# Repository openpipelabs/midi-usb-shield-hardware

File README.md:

OpenPipe MIDI-USB Shield
========================

This is the PCB for the OpenPipe MIDI-USB Shield  
Format is EagleCAD schematic and board layout  

For more details, check out the product page at  
http://openpipe.cc/products/midi-usb-shield/

OpenPipe invests time and resources providing this open source design, 
please support OpenPipe and open-source hardware by purchasing 
products from OpenPipe!

License & Attribution
---------------------
Designed by OpenPipe (www.openpipe.cc).

Creative Commons Attribution-NonCommercial-ShareAlike license (CC BY-NC-SA)

http://creativecommons.org/licenses/by-nc-sa/3.0/  
http://creativecommons.org/licenses/by-nc-sa/3.0/legalcode

All text above must be included in any redistribution

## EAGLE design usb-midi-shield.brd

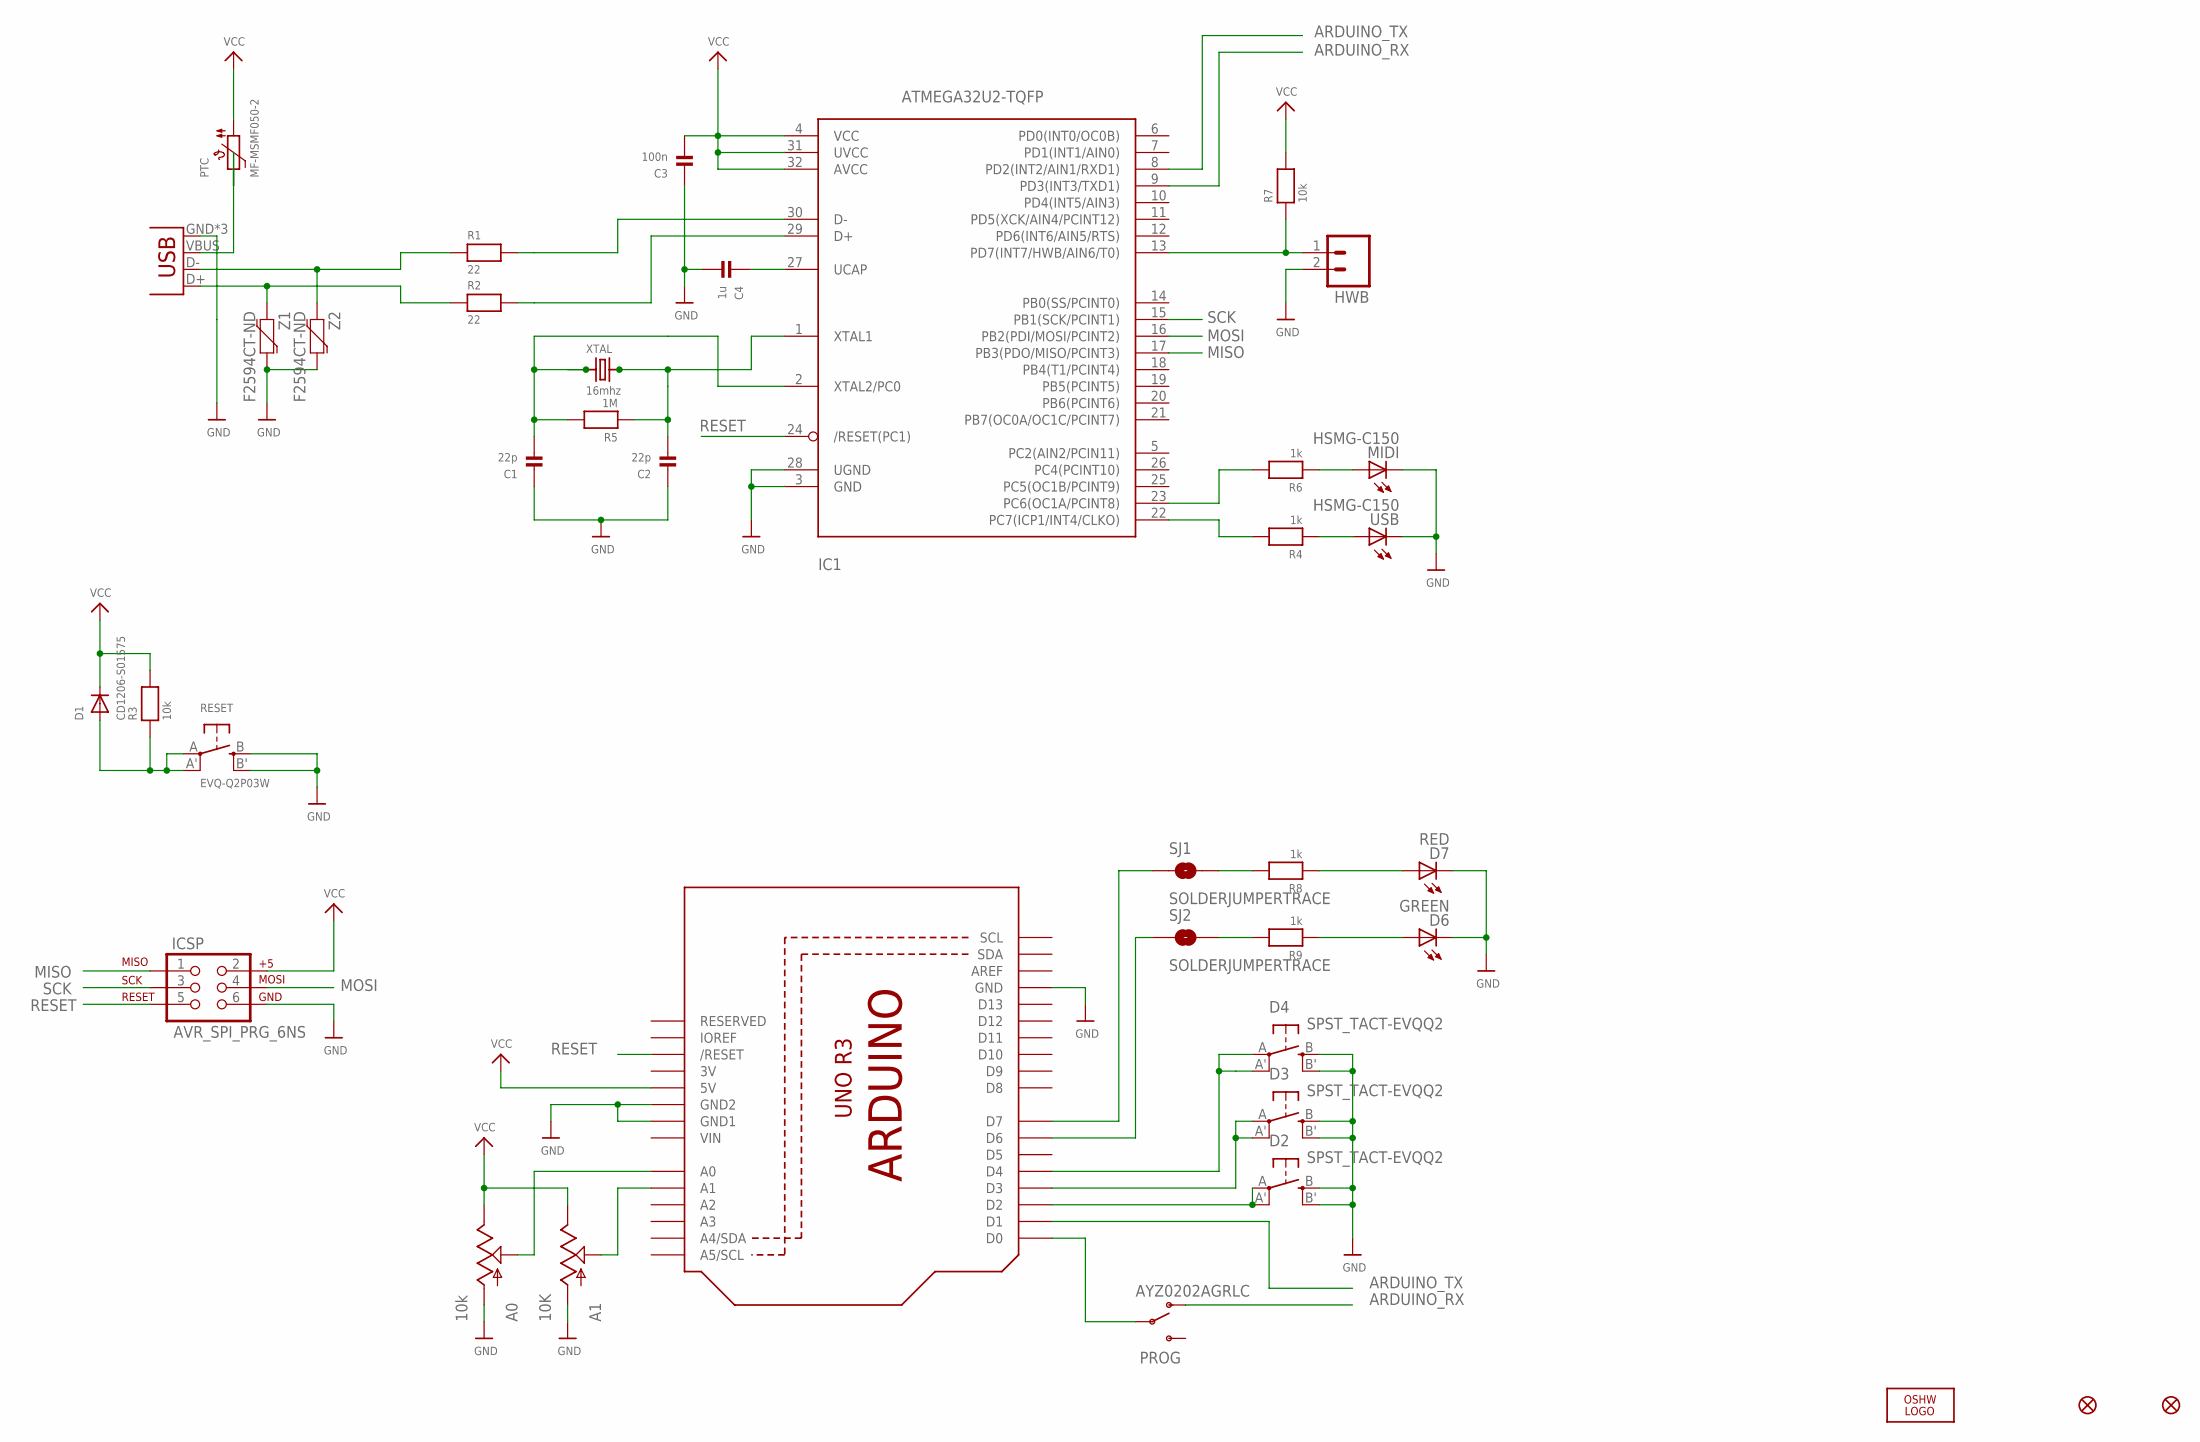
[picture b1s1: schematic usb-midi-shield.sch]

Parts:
A0: 10k; ALPS_POT
A1: 10K; ALPS_POT
C1, C2: 22p; 0603
C3: 100n; 0603
C4: 1u; 0603
D1: CD1206-S01575; SOD-123
D2, D3, D4: SPST_TACT-EVQQ2; EVQ-Q2
D6: GREEN; LED-1206
D7: RED; LED-1206
FID1, FID2: FIDUCIAL1.5X3; FIDUCIAL-1.5X3
HWB: M02LOCK; 1X02_LOCK
IC1: ATMEGA32U2-TQFP; TQFP32-08
ICSP: AVR_SPI_PRG_6NS; 2X3-NS
JP1: USB-MICROB
LOGO1: OSHW_LOGO_FILLX0350-NT; OSHW_FILLX350_NOTEXT
MIDI: HSMG-C150; LED-1206
PROG: AYZ0202AGRLC; AYZ0202
PTC: MF-MSMF050-2; PTC1812
R1, R2: 22; 0805
R3, R7: 10k; 0805
R4, R6, R8, R9: 1k; 0805
R5: 1M; 0805
RESET: EVQ-Q2P03W; EVQ-Q2
SJ1, SJ2: SOLDERJUMPERTRACE; SJ_2S-TRACE
U1: ARDUINOR3NODIM; ARDUINOR3-NODIM
USB: HSMG-C150; LED-1206
XTAL: 16mhz; HC49UP
Z1, Z2: F2594CT-ND; 0603-RES

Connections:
3V: U1.3V
ARDUINO_RX: IC1.9 (PD3(INT3/TXD1)), PROG.1 (O)
ARDUINO_TX: IC1.8 (PD2(INT2/AIN1/RXD1)), U1.D1
D-: IC1.29 (D+), R2.2
GND: A0.P$3 (A), A1.P$3 (A), C1.1, C2.1, C3.1, C4.2, D2.B (S), D2.B' (S1), D3.B (S), D3.B' (S1), D4.B (S), D4.B' (S1), D6.C, D7.C, HWB.2, IC1.3 (GND), IC1.28 (UGND), ICSP.6, JP1.GND, JP1.MT1 (GND), JP1.MT2 (GND), MIDI.C, RESET.B (S), RESET.B' (S1), U1.GND, U1.GND1, U1.GND2, USB.C, Z1.2, Z2.2
MISO: IC1.17 (PB3(PDO/MISO/PCINT3)), ICSP.1
MOSI: IC1.16 (PB2(PDI/MOSI/PCINT2)), ICSP.4
unnamed: HWB.1, IC1.13 (PD7(INT7/HWB/AIN6/T0)), R7.1
unnamed: C1.2, IC1.2 (XTAL2/PC0), R5.2, XTAL.1
unnamed: JP1.D+, R2.1, Z1.1
unnamed: C2.2, IC1.1 (XTAL1), R5.1, XTAL.2
unnamed: IC1.30 (D-), R1.2
unnamed: D2.A, D2.A' (P1), U1.D2
unnamed: D3.A, D3.A' (P1), U1.D3
unnamed: C4.1, IC1.27 (UCAP)
unnamed: JP1.VBUS, PTC.P$2 (2)
unnamed: IC1.23 (PC6(OC1A/PCINT8)), R6.2
unnamed: IC1.22 (PC7(ICP1/INT4/CLKO)), R4.2
unnamed: MIDI.A, R6.1
unnamed: R4.1, USB.A
unnamed: D4.A, D4.A' (P1), U1.D4
unnamed: JP1.D-, R1.1, Z2.1
unnamed: A1.P$2 (S), U1.A1
unnamed: A0.P$2 (S), U1.A0
unnamed: R8.2, SJ1.2
unnamed: D7.A, R8.1
unnamed: R9.2, SJ2.2
unnamed: D6.A, R9.1
unnamed: SJ2.1, U1.D6
unnamed: SJ1.1, U1.D7
unnamed: PROG.2, U1.D0
RESET: D1.A, IC1.24 (/RESET(PC1)), ICSP.5, R3.1, RESET.A, RESET.A' (P1), U1.RESET (/RESET)
SCK: IC1.15 (PB1(SCK/PCINT1)), ICSP.3
VCC: A0.P$1 (E), A1.P$1 (E), C3.2, D1.C, IC1.4 (VCC), IC1.31 (UVCC), IC1.32 (AVCC), ICSP.2, PTC.P$1 (1), R3.2, R7.2, U1.5V
VIN: U1.VIN

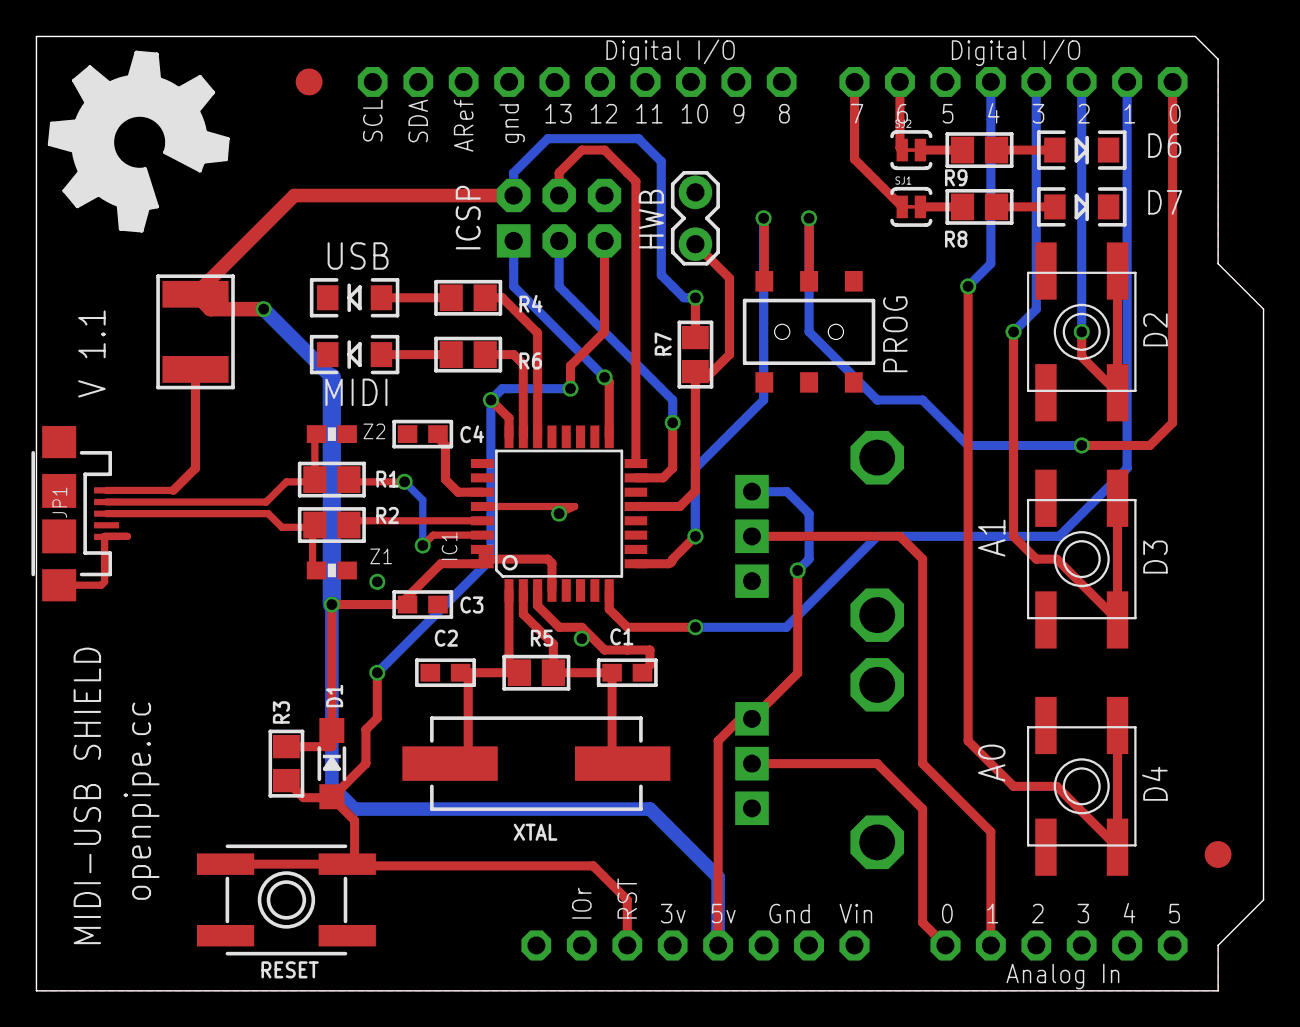
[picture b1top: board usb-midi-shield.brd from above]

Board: 2 copper layers, 68.6 x 53.3 mm, 39 parts (0 on the bottom side), 33 nets.

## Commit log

2012-12-23 initial hardware version
2012-12-30 updated README with license information
2012-12-30 README updated
2012-12-30 .project deleted
2013-03-09 PDF added
2013-06-25 changed to v1.1
2013-06-25 deleted unwanted file

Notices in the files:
parts and their libraries:
microbuilder: This work is placed in the public domain, and may be freely used for commercial and non-commercial work with the following conditions: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
SparkFun-Electromechanical: Licensing: CC v3.0 Share-Alike You are welcome to use this library for commercial purposes.
